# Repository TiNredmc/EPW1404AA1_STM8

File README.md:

# EPW1404AA1_STM8
EPW1404AA1 running with STM8L151F3 

Buying links
=

[EPW1404AA1](https://www.aliexpress.com/item/1005002238967941.html).  
[Hirose 11 pin 0.3mm connector](https://www.aliexpress.com/item/32849471537.html).  
[PCB @OSHPark](https://oshpark.com/).  

Source Code
=

Dev source code can be found on my [stm8l_sdcc_template repo](https://github.com/TiNredmc/stm8l_sdcc_template/tree/master/code/EPW1404AA1_SSD1316)  
Watch source code can be found on my [stm8l_sdcc_template repo too](https://github.com/TiNredmc/stm8l_sdcc_template/tree/master/code/Fl3xWatchOLED)

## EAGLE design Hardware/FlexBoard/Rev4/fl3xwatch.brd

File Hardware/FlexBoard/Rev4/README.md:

# Rev 4

This is Rev4 shcematic and board. Fixed the connector.

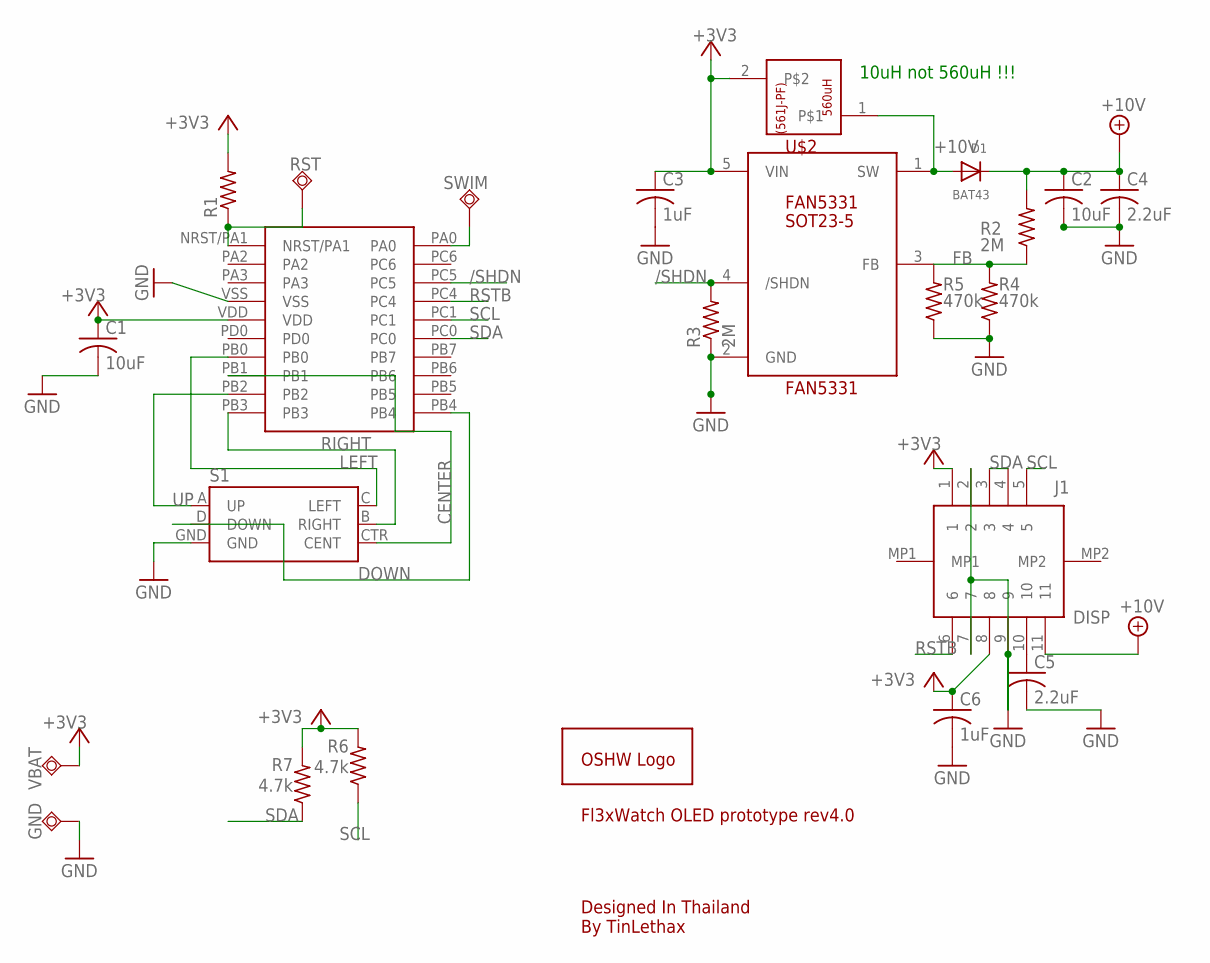
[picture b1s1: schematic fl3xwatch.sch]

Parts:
C1, C2: 10uF; C0805
C3, C6: 1uF; C0603
C4, C5: 2.2uF; C0603
D1: BAT43; SOD-323F
GND: TPSQTP20SQ; TP20SQ
GOLD_ORB_SM1: OSHWLOGOLOGO5MM; OSHW_5MM
J1: DISP; FH35C11S03SHW50
L1: 10uH; INDC4526X50N
R1: R-US_R0603; R0603
R2, R3: 2M; R0603
R4, R5: 470k; R0805
R6, R7: 4.7k; R0603
RST: TPSQTP15R; TP15R
S1: SPARKFUN-ELECTROMECHANICAL_JOYSTICK_MINI
SWIM: TPSQTP15R; TP15R
U$1: STM8L151F3; UFQFPN-20
U$2: FAN5331; SOT95P280X145-5N
VBAT: TPSQTP20SQ; TP20SQ

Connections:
+3V3: C1.1, C3.1, C6.1, J1.1, J1.8, L1.2, R1.2, R6.2, R7.2, U$1.VDD, U$2.5 (VIN), VBAT.TP
+10V: C2.1, C4.1, D1.C, J1.11, R2.2
/SHDN: R3.2, U$1.PC5, U$2.4 (/SHDN)
CENTER: S1.CTR (CENT), U$1.PB1
DOWN: S1.D (DOWN), U$1.PB4
FB: R2.1, R4.2, R5.2, U$2.3 (FB)
GND: C1.2, C2.2, C3.2, C4.2, C5.2, C6.2, GND.TP, J1.2, J1.7, J1.9, R3.1, R4.1, R5.1, S1.GND, U$1.VSS, U$2.2 (GND)
LEFT: S1.C (LEFT), U$1.PB0
unnamed: R1.1, RST.TP, U$1.NRST/PA1
unnamed: C5.1, J1.10
RIGHT: S1.B (RIGHT), U$1.PB3
RSTB: J1.6, U$1.PC4
SCL: J1.5, R6.1, U$1.PC1
SDA: J1.3, J1.4, R7.1, U$1.PC0
SW: D1.A, L1.1, U$2.1 (SW)
SWIM: SWIM.TP, U$1.PA0
UP: S1.A (UP), U$1.PB2

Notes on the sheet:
10uH not 560uH !!!
Fl3xWatch OLED prototype rev4.0
Designed In Thailand By TinLethax

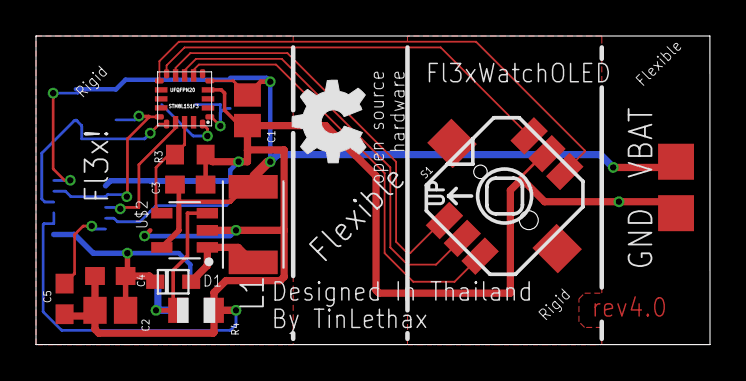
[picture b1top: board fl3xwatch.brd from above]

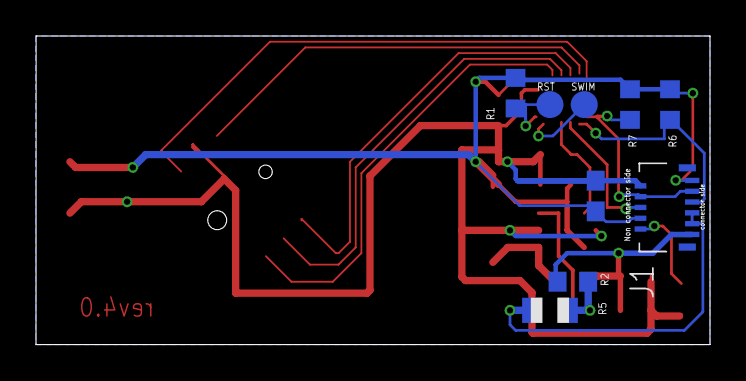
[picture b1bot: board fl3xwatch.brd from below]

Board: 2 copper layers, 37.4 x 17.1 mm, 24 parts (9 on the bottom side), 17 nets.

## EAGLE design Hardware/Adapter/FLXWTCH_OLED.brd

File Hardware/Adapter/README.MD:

BOM list. 
1. FH35C-11S-0.3SHW x1
2. 2.2uF 25v 0605 x2
3. 1uF 16v 0605 x1
4. 4.7kOhm x2 
5. 1x3 pin header 2.54mm x2

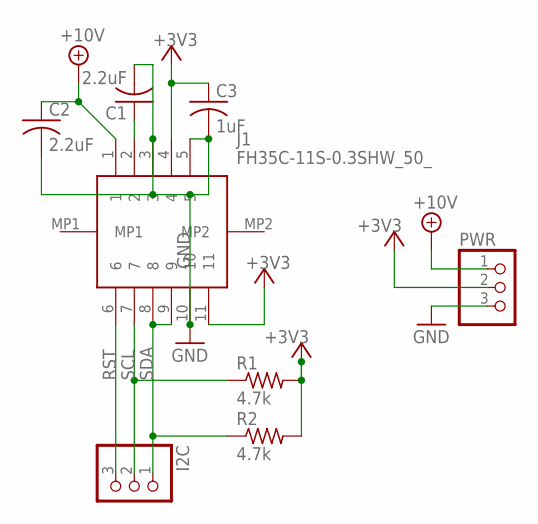
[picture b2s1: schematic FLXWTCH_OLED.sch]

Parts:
C1, C2: 2.2uF; C0603K
C3: 1uF; C0603K
I2C: PINHD-1X3; 1X03
J1: FH35C-11S-0.3SHW_50_; FH35C11S03SHW50
PWR: PINHD-1X3; 1X03
R1, R2: 4.7k; R0603

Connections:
+3V3: C3.1, J1.4, J1.11, PWR.2, R1.2, R2.2
+10V: C2.1, J1.1, PWR.1
GND: C1.2, C2.2, C3.2, J1.3, J1.5, J1.10, PWR.3
unnamed: C1.1, J1.2
RST: I2C.3, J1.6
SCL: I2C.2, J1.7, R1.1
SDA: I2C.1, J1.8, J1.9, R2.1

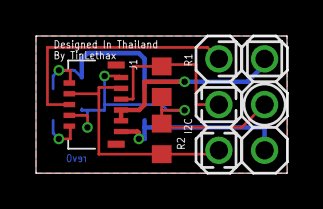
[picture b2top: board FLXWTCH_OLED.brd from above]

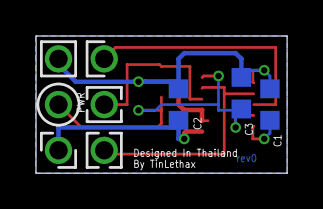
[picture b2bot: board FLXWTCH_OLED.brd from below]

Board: 2 copper layers, 13.9 x 7.6 mm, 8 parts (3 on the bottom side), 7 nets.

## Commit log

2021-08-22 Datasheet of EPW1404AA1
    Provided by https://www.aliexpress.com/item/1005002238967941.html
2021-08-22 added BOM list
2021-08-22 Rev0 Schematic and Board
2021-08-22 Added links to buy stuffs
2021-09-01 Added link to code
2021-09-01 Added link to buy the PCB at OSHPark
2021-09-06 Added Power design guide.
2021-09-07 Added Warning
2021-09-07 added schematic and board file
2021-09-09 Update PCB link to rev 2.0 and repo links
2021-09-09 rev2 readme
2021-09-09 added board and sch of rev2.0
2021-09-09 Rev2.1 board
2021-09-09 Added rev2.1 change log
2021-09-19 added Rev 2.2 PCB
2021-09-19 added rev 2.2 update
2021-09-19 added link to rev 2.2 on OSHPark
2021-09-26 rev 3 board changelog
2021-09-26 rev3.1
2021-09-28 rev 2.1
    corrected the inductor value. user
2021-11-08 removed due to design error.
2021-11-08 notice
2021-11-08 Rev4
2021-11-08 rev4 board and schematic.
2021-11-08 removed link to PCB, prevent you from my failure.
